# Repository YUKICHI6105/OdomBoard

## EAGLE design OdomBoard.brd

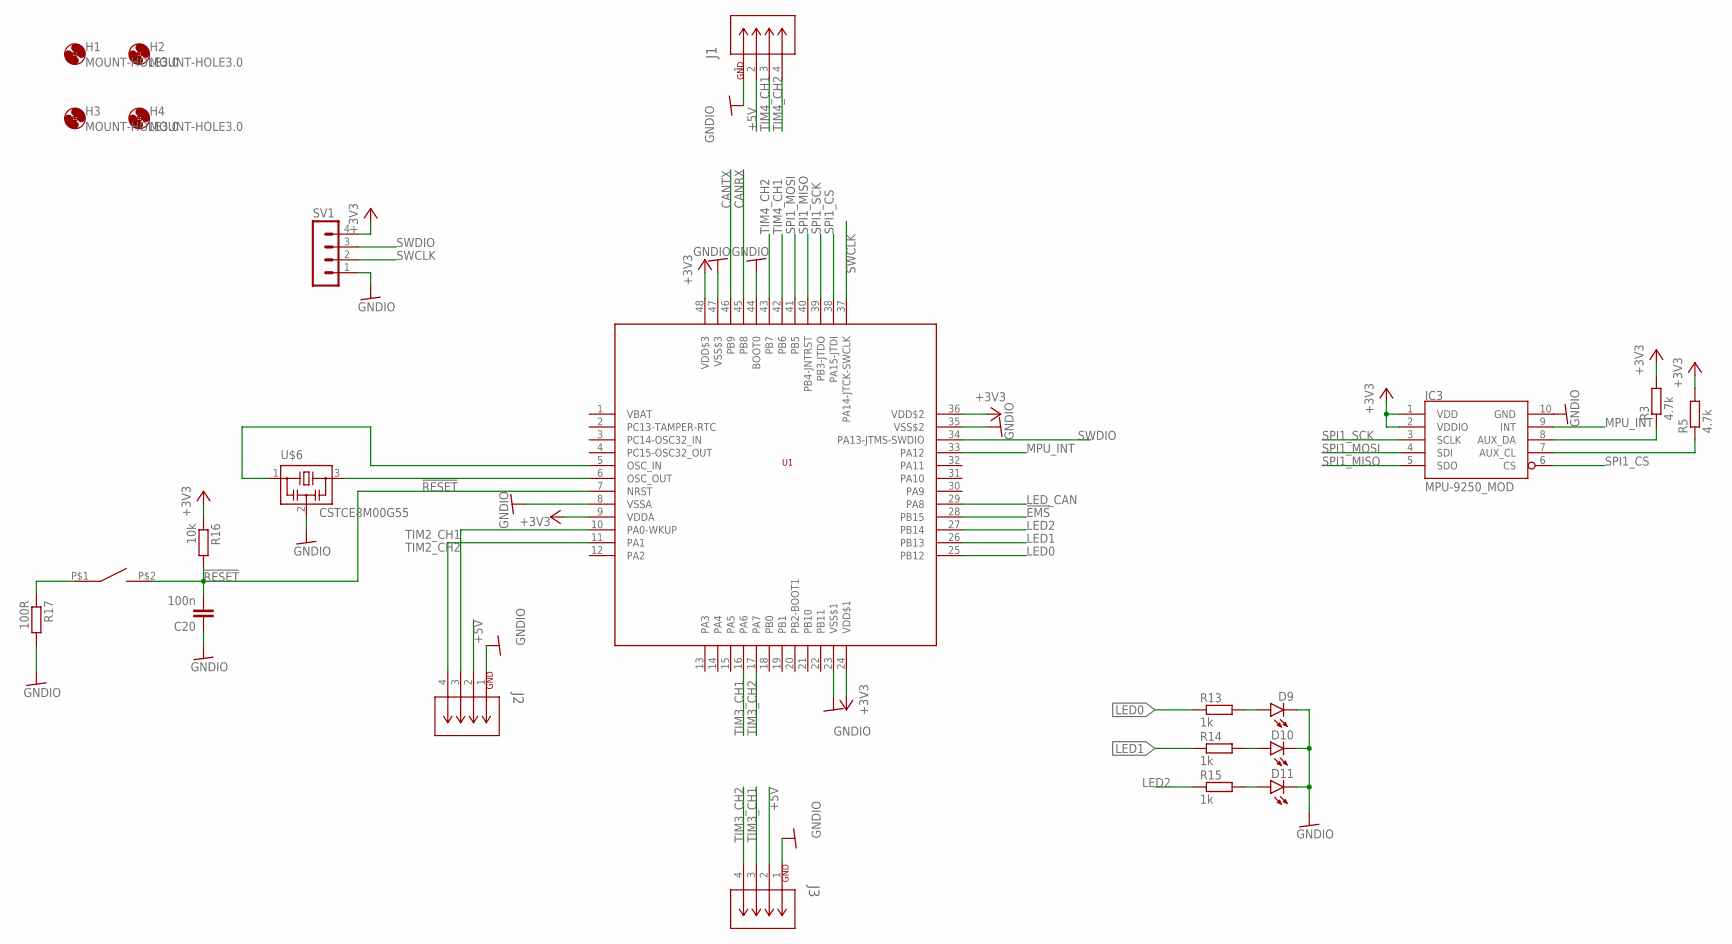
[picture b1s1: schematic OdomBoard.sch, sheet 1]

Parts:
C20: 100n; C0603
D9, D10, D11: LEDCHIPLED_0805; CHIPLED_0805
H1, H2, H3, H4: MOUNT-HOLE3.0; 3,0
IC3: MPU-9250_MOD; MPU_9250_MOD
J1, J2, J3: EP2.5-4-SIDE; CONN4_1744426-4
R3, R5: 4.7k; R0603
R13, R14, R15: 1k; R0603
R16: 10k; R0603
R17: 100R; R0603
SV1: MA04-1
SW1: SWITCH_TACTILETOP; SWITCH_TACTILE_3X6
U1: STM32F103C8; LQFP48
U$6: CSTCE8M00G55

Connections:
!EMS: U1.28 (PB15); also elsewhere on the board
!RESET: C20.2, R16.2, SW1.P$2 (2), U1.7 (NRST)
+3V3: IC3.1 (VDD), IC3.2 (VDDIO), R3.2, R5.2, R16.1, SV1.4, U1.9 (VDDA), U1.24 (VDD$1), U1.36 (VDD$2), U1.48 (VDD$3); also elsewhere on the board
+5V: J1.2, J2.2, J3.2; also elsewhere on the board
CANRX: U1.45 (PB8); also elsewhere on the board
CANTX: U1.46 (PB9); also elsewhere on the board
GNDIO: C20.1, D9.C, D10.C, D11.C, IC3.10 (GND), J1.1, J2.1, J3.1, R17.2, SV1.1, U1.8 (VSSA), U1.23 (VSS$1), U1.35 (VSS$2), U1.44 (BOOT0), U1.47 (VSS$3), U$6.2; also elsewhere on the board
LED0: R13.1, U1.25 (PB12)
LED1: R14.1, U1.26 (PB13)
LED2: R15.1, U1.27 (PB14)
LED_CAN: U1.29 (PA8); also elsewhere on the board
MPU_INT: IC3.9 (INT), U1.33 (PA12)
unnamed: IC3.8 (AUX_DA), R3.1
unnamed: IC3.7 (AUX_CL), R5.1
unnamed: D10.A, R14.2
unnamed: D9.A, R13.2
unnamed: U1.6 (OSC_OUT), U$6.3
unnamed: R17.1, SW1.P$1 (1)
unnamed: U1.5 (OSC_IN), U$6.1
unnamed: D11.A, R15.2
SPI1_CS: IC3.6 (CS), U1.38 (PA15-JTDI)
SPI1_MISO: IC3.5 (SDO), U1.40 (PB4-JNTRST)
SPI1_MOSI: IC3.4 (SDI), U1.41 (PB5)
SPI1_SCK: IC3.3 (SCLK), U1.39 (PB3-JTDO)
SWCLK: SV1.2, U1.37 (PA14-JTCK-SWCLK)
SWDIO: SV1.3, U1.34 (PA13-JTMS-SWDIO)
TIM2_CH1: J2.3, U1.10 (PA0-WKUP)
TIM2_CH2: J2.4, U1.11 (PA1)
TIM3_CH1: J3.3, U1.16 (PA6)
TIM3_CH2: J3.4, U1.17 (PA7)
TIM4_CH1: J1.3, U1.42 (PB6)
TIM4_CH2: J1.4, U1.43 (PB7)

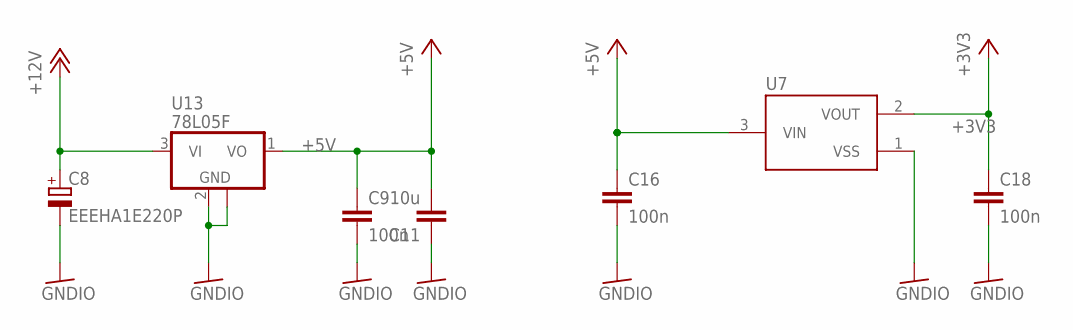
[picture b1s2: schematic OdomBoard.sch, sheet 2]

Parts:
C8: EEEHA1E220P; 153CLV-0605
C9, C16, C18: 100n; C0603
C11: 10u; C1210
U7: XC6206; SOT95P240X110-3
U13: 78L05F; SOT89

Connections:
+3V3: C18.1, U7.2 (VOUT); also elsewhere on the board
+5V: C9.1, C11.2, C16.1, U7.3 (VIN), U13.1 (VO); also elsewhere on the board
+12V: C8.+, U13.3 (VI); also elsewhere on the board
GNDIO: C8.-, C9.2, C11.1, C16.2, C18.2, U7.1 (VSS), U13.2 (GND), U13.2@1 (GND); also elsewhere on the board

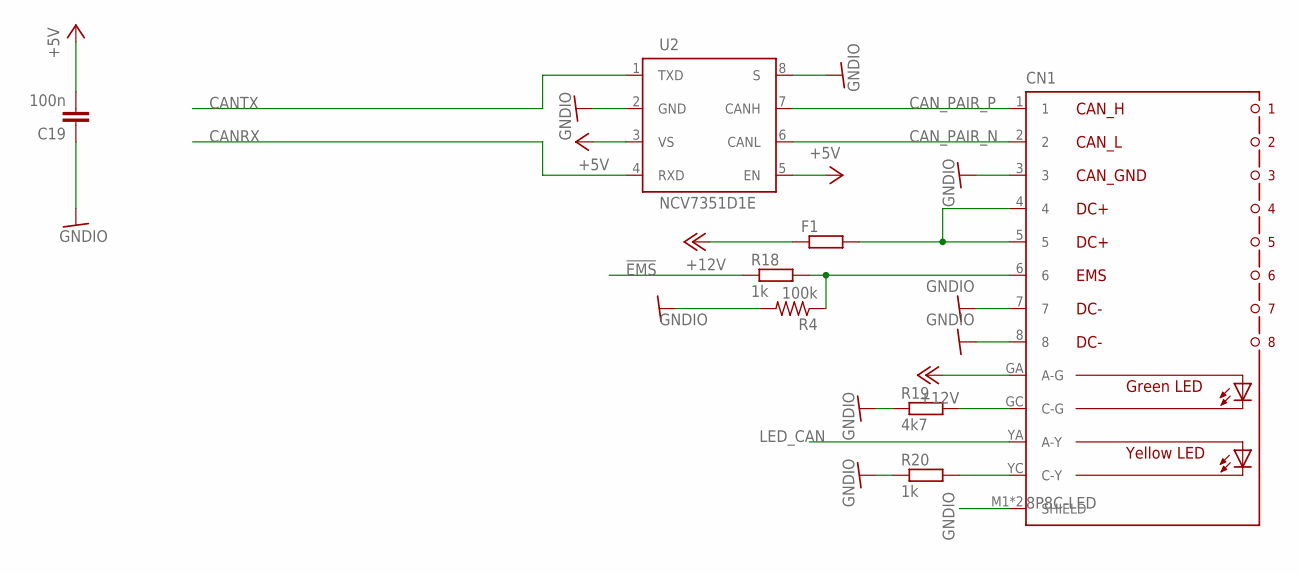
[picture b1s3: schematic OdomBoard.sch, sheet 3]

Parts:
C19: 100n; C0603
CN1: 8P8C-LED
F1: R-EU_R1206; R1206
R4: 100k; R0603
R18, R20: 1k; R0603
R19: 4k7; R0603
U2: NCV7351D1E; SO08

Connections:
!EMS: R18.1; also elsewhere on the board
+5V: C19.2, U2.3 (VS), U2.5 (EN); also elsewhere on the board
+12V: CN1.GA (A-G), F1.1; also elsewhere on the board
CANRX: U2.4 (RXD); also elsewhere on the board
CANTX: U2.1 (TXD); also elsewhere on the board
CAN_PAIR_N: CN1.2, U2.6 (CANL)
CAN_PAIR_P: CN1.1, U2.7 (CANH)
GNDIO: C19.1, CN1.3, CN1.7, CN1.8, CN1.M1 (SHIELD), CN1.M2 (SHIELD), R4.2, R19.1, R20.1, U2.2 (GND), U2.8 (S); also elsewhere on the board
LED_CAN: CN1.YA (A-Y); also elsewhere on the board
unnamed: CN1.4, CN1.5, F1.2
unnamed: CN1.YC (C-Y), R20.2
unnamed: CN1.GC (C-G), R19.2
unnamed: CN1.6, R4.1, R18.2

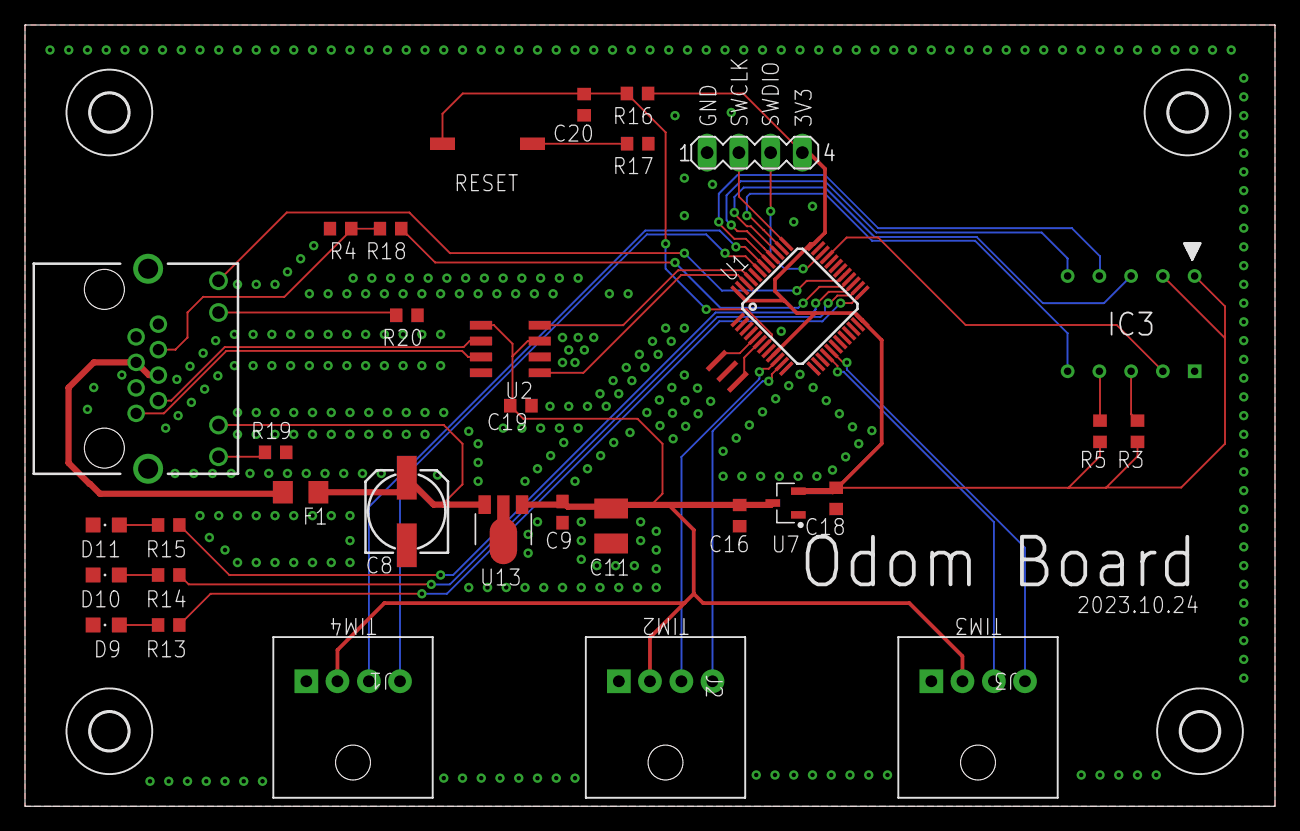
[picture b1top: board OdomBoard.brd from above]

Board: 2 copper layers, 100.0 x 62.5 mm, 38 parts (0 on the bottom side), 39 nets.

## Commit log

2023-10-24 First Version
